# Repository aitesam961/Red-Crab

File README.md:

# Red-Crab: An Open Source, Modular PID controller.
RED-CRAB is an Open Source PID Controller designed for easy and flexible prototyping with PID controllers.
Offering vast selection of control parameters, this Project could be implemented in applications from hobbyist projects to home devices to industrial equipment where closed loop systems are required.

The idea of this project is to use a modular approach where different ad-ons could be used with the Basic PID controller board for controlling applications. Add-on Boards will be designed next added to the repository.
(OSHW Community can contribute in designing add-ons).

## Preview

## Table of contents
* [Red-Crab Overview](https://github.com/aitesam961/Red-Crab/blob/main/README.md#red-crab-overview)
* [How to Use:](https://github.com/aitesam961/Red-Crab/blob/main/README.md#how-to-use)
* [Electrical Specifications](https://github.com/aitesam961/Red-Crab/blob/main/README.md#electrical-specifications)
* [Build Your Own?](https://github.com/aitesam961/Red-Crab/blob/main/README.md#build-your-own)
* [Future Plans](https://github.com/aitesam961/Red-Crab/blob/main/README.md#future-plans)
* [Ordering Info](https://github.com/aitesam961/Red-Crab/blob/main/README.md#ordering-info)
* [Frequently Asked Questions(FAQs)](https://github.com/aitesam961/Red-Crab/blob/main/README.md#frequently-asked-questionsfaqs)
* [General Component Info](https://github.com/aitesam961/Red-Crab/blob/main/README.md#general-component-info)
* [Acknowledgements](https://github.com/aitesam961/Red-Crab/blob/main/README.md#acknowledgements)
* [License](https://github.com/aitesam961/Red-Crab/blob/main/README.md#license)

# Red-Crab Overview
### Features:
* Selectable P,PI,PID configurations.
* Adjustable GAINs using 50kOHM Potentiometers.
* DIP Switches for Controller Configuration
* Wide DC Voltage Input Range 
* 4-Layer Board with special Care to EMC/EMI for use in commercial applications.
* Open Source under GPL 3.0. (See License)
* Integrated Output Current Aplification for Larger Loads
* Ability to power External Peripherals

## How to Use:
## Electrical Specifications:

## Build Your Own?
## Future Plans
In future, this project seeks improvements and Development in following areas:
* Digital to Analog Converter Module (Ad-On Board)
* Temeprature Sensing & Amplification (Ad-On Board)
* Frequency to Voltage Converter (Ad-On Board)
* Integration with ARDUINO for Data Logging (Ad-On Board)
* Servo Actuation Control (Ad-On Board)
* Disturbance Integration Using Arduino (Ad-On Board)
## Ordering Info
You Can manufacture the PCBs from PCBWay.
[Check Out PCBWay](https://www.pcbway.com/setinvite.aspx?inviteid=440401)

Note: I am not affiliated with PCBWay. However, I just like their service and build quality.

## Frequently Asked Questions(FAQs)
## General Component Info

## Roadmap

* [x] Concept Proof
* [x] Research & Information
* [x] Finalizing The Idea
* [x] Schematics
* [x] PCB Design
* [ ] Validation & Testing
* [x] Documentation
* [ ] Future Improvements

### Contributions

Contributions are what make the open source community such an amazing place to learn, inspire, and create. Any contributions you make are **greatly appreciated**.

If you have a suggestion that would make this better, please fork the repo and create a pull request. You can also simply open an issue with the tag "enhancement".
Don't forget to give the project a star! Thanks again!

1. Fork the Project
2. Create your Feature Branch (`git checkout -b feature/AmazingFeature`)
3. Commit your Changes (`git commit -m 'Add some AmazingFeature'`)
4. Push to the Branch (`git push origin feature/AmazingFeature`)
5. Open a Pull Request

## Acknowledgements
This project is created to serve the Open Hardware Community in terms of Analog Controller Design using discrete components. Unfortunately, there isn't much of open source projects in terms of Flexible and Modular PID controller Design area.
Thye crater hopes it helps someone

## File Tree
```
.
├── Documents
│   ├── ibom.html
│   └── PID_Controller_Design.pdf
├── Images
│   ├── BOT1.png
│   ├── BOT1_RT.png
│   ├── PCB_1.png
│   ├── SID1_RT.png
│   ├── TOP1.png
│   ├── TOP1_RT.png
│   ├── TOP2_RT.png
│   ├── TOP3_RT.png
│   └── TOP4_RT.png
├── LICENSE.txt
├── Manufacturing Files
│   ├── bom.csv
│   ├── designators.csv
│   ├── gerber.zip
│   ├── netlist.ipc
│   └── positions.csv
├── MCAD Files
│   ├── Red-Crab.step
│   └── Red-Crab.wrl
├── README.md
├── Readme.txt.txt
├── References
│   ├── BananaSchplit-master
│   │   └── BananaSchplit-master
│   │       ├── assembly
│   │       │   ├── BananaSchplit-BOM.csv
│   │       │   └── BananaSchplit-Footprint-Positions.csv
│   │       ├── BananaSchplit-cache.lib
│   │       ├── BananaSchplit.kicad_pcb
│   │       ├── BananaSchplit.kicad_pcb-bak
│   │       ├── BananaSchplit.net
│   │       ├── BananaSchplit.pro
│   │       ├── BananaSchplit-rescue.dcm
│   │       ├── BananaSchplit-rescue.lib
│   │       ├── BananaSchplit.sch
│   │       ├── BananaSchplit.sch-bak
│   │       ├── BananaSchplit.xml
│   │       ├── fp-info-cache
│   │       ├── fp-lib-table
│   │       ├── gerber
│   │       │   ├── BananaSchplit-B_Cu.gbr
│   │       │   ├── BananaSchplit-B_Mask.gbr
│   │       │   ├── BananaSchplit-B_Paste.gbr
│   │       │   ├── BananaSchplit-B_SilkS.gbr
│   │       │   ├── BananaSchplit.drl
│   │       │   ├── BananaSchplit-Edge_Cuts.gbr
│   │       │   ├── BananaSchplit-F_Cu.gbr
│   │       │   ├── BananaSchplit-F_Mask.gbr
│   │       │   ├── BananaSchplit-F_Paste.gbr
│   │       │   ├── BananaSchplit-F_SilkS.gbr
│   │       │   └── BananaSchplit-Gerber.zip
│   │       ├── lib
│   │       │   ├── BananSchplitSilk.pretty
│   │       │   │   ├── BananaSchplitDrawn.png
│   │       │   │   ├── BananaSchplit.png
│   │       │   │   ├── BananaSchplitSilkLogoDrawn.kicad_mod
│   │       │   │   └── BananaSchplitSilkLogo.kicad_mod
│   │       │   ├── TPS65131RGET.lib
│   │       │   ├── TPS65131RGET.mod
│   │       │   └── TPS65131RGET.stp
│   │       ├── LICENSE
│   │       ├── README.md
│   │       └── sym-lib-table
│   ├── Screenshot 2022-07-08 204516.png
│   └── The_Design_of_the_PID_Controller.pdf
└── Source Files
    └── Red_Crab_KiCAD_Source
        ├── fp-info-cache
        ├── Passives.kicad_sch
        ├── PID_Core.kicad_sch
        ├── place_footprints.log
        ├── Power.kicad_sch
        ├── Red-Crab.kicad_pcb
        ├── Red-Crab.kicad_prl
        ├── Red-Crab.kicad_pro
        ├── Red-Crab.kicad_sch
        └── shapes3D
            ├── C_0603_1608Metric.wrl
            ├── C_0805_2012Metric.wrl
            ├── C_1206_3216Metric.wrl
            ├── CP_Elec_6.3x5.3.wrl
            ├── CP_Elec_6.3x7.7.wrl
            ├── DC-jack.wrl
            ├── D_SOD-123.wrl
            ├── Fuse_1210_3225Metric.wrl
            ├── HSOP-8-1EP_3.9x4.9mm_P1.27mm_EP2.41x3.1mm.wrl
            ├── HTSOP-8-1EP_3.9x4.9mm_Pitch1.27mm.wrl
            ├── JST_EH_S6B-EH_1x06_P2.50mm_Horizontal.wrl
            ├── L_Bourns_SRR1260.wrl
            ├── LED_0805_2012Metric.wrl
            ├── POT_SMD.wrl
            ├── QFN-24-1EP_4x4mm_P0.5mm_EP2.6x2.6mm.wrl
            ├── R_0402_1005Metric.wrl
            ├── R_0603_1608Metric.wrl
            ├── SOIC-14_3.9x8.7mm_P1.27mm.wrl
            ├── SOT-23.wrl
            └── SW_DIP_SPSTx08_Slide_6.7x21.88mm_W8.61mm_P2.54mm_LowProfile.wrl

14 directories, 87 files
```
## License
This Project is published under General Public License V3.0 See `LICENSE.txt` for more information.
> https://www.gnu.org/licenses/quick-guide-gplv3.html

<p align="right">(<a href="#top">back to top</a>)</p>

* [Jump To Start](https://github.com/maitesam/OpenADSP/blob/main/README.md#Description)

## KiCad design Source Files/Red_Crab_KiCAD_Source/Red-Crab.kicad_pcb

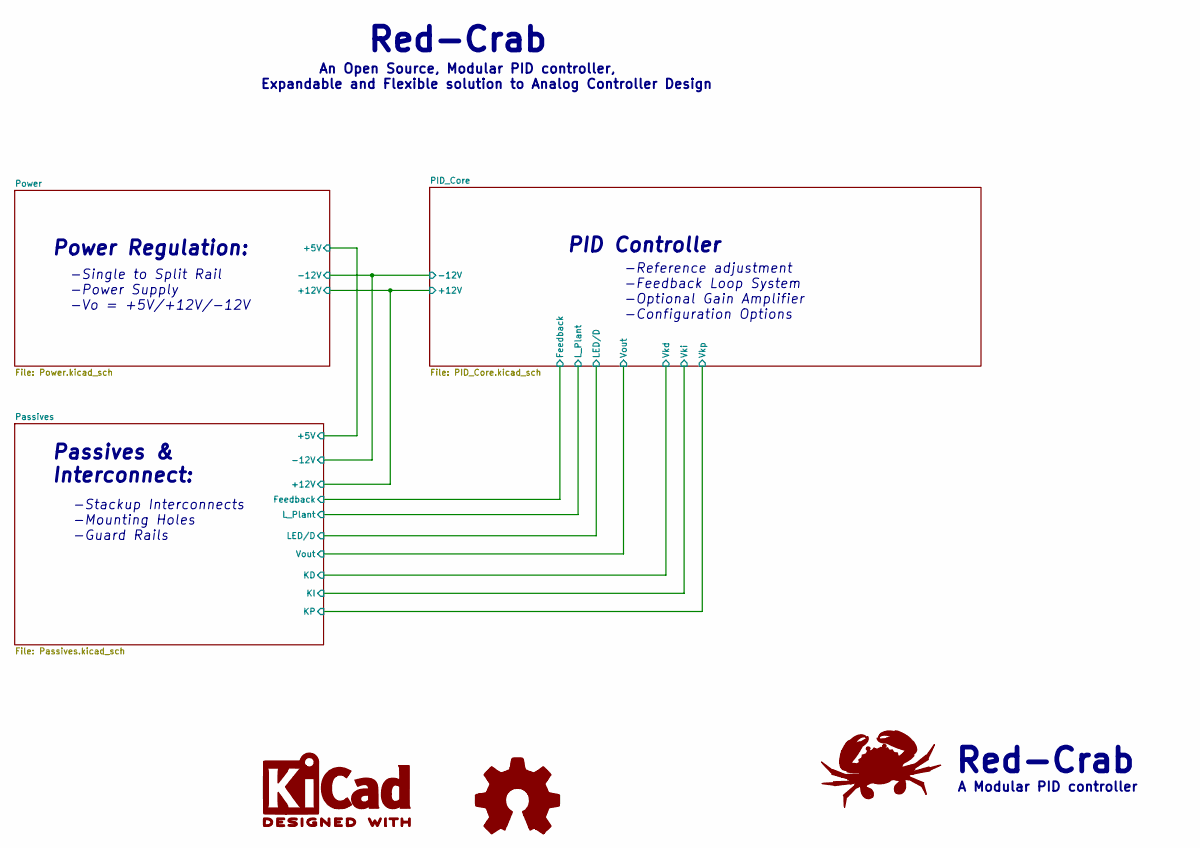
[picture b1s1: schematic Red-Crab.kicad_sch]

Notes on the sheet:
Passives & Interconnect:
An Open Source, Modular PID controller, Expandable and Flexible solution to Analog Controller Design
Red-Crab
PID Controller
Power Regulation:
-Single to Split Rail -Power Supply -Vo = +5V/+12V/-12V
A Modular PID controller
-Stackup Interconnects -Mounting Holes -Guard Rails
-Reference adjustment -Feedback Loop System -Optional Gain Amplifier -Configuration Options

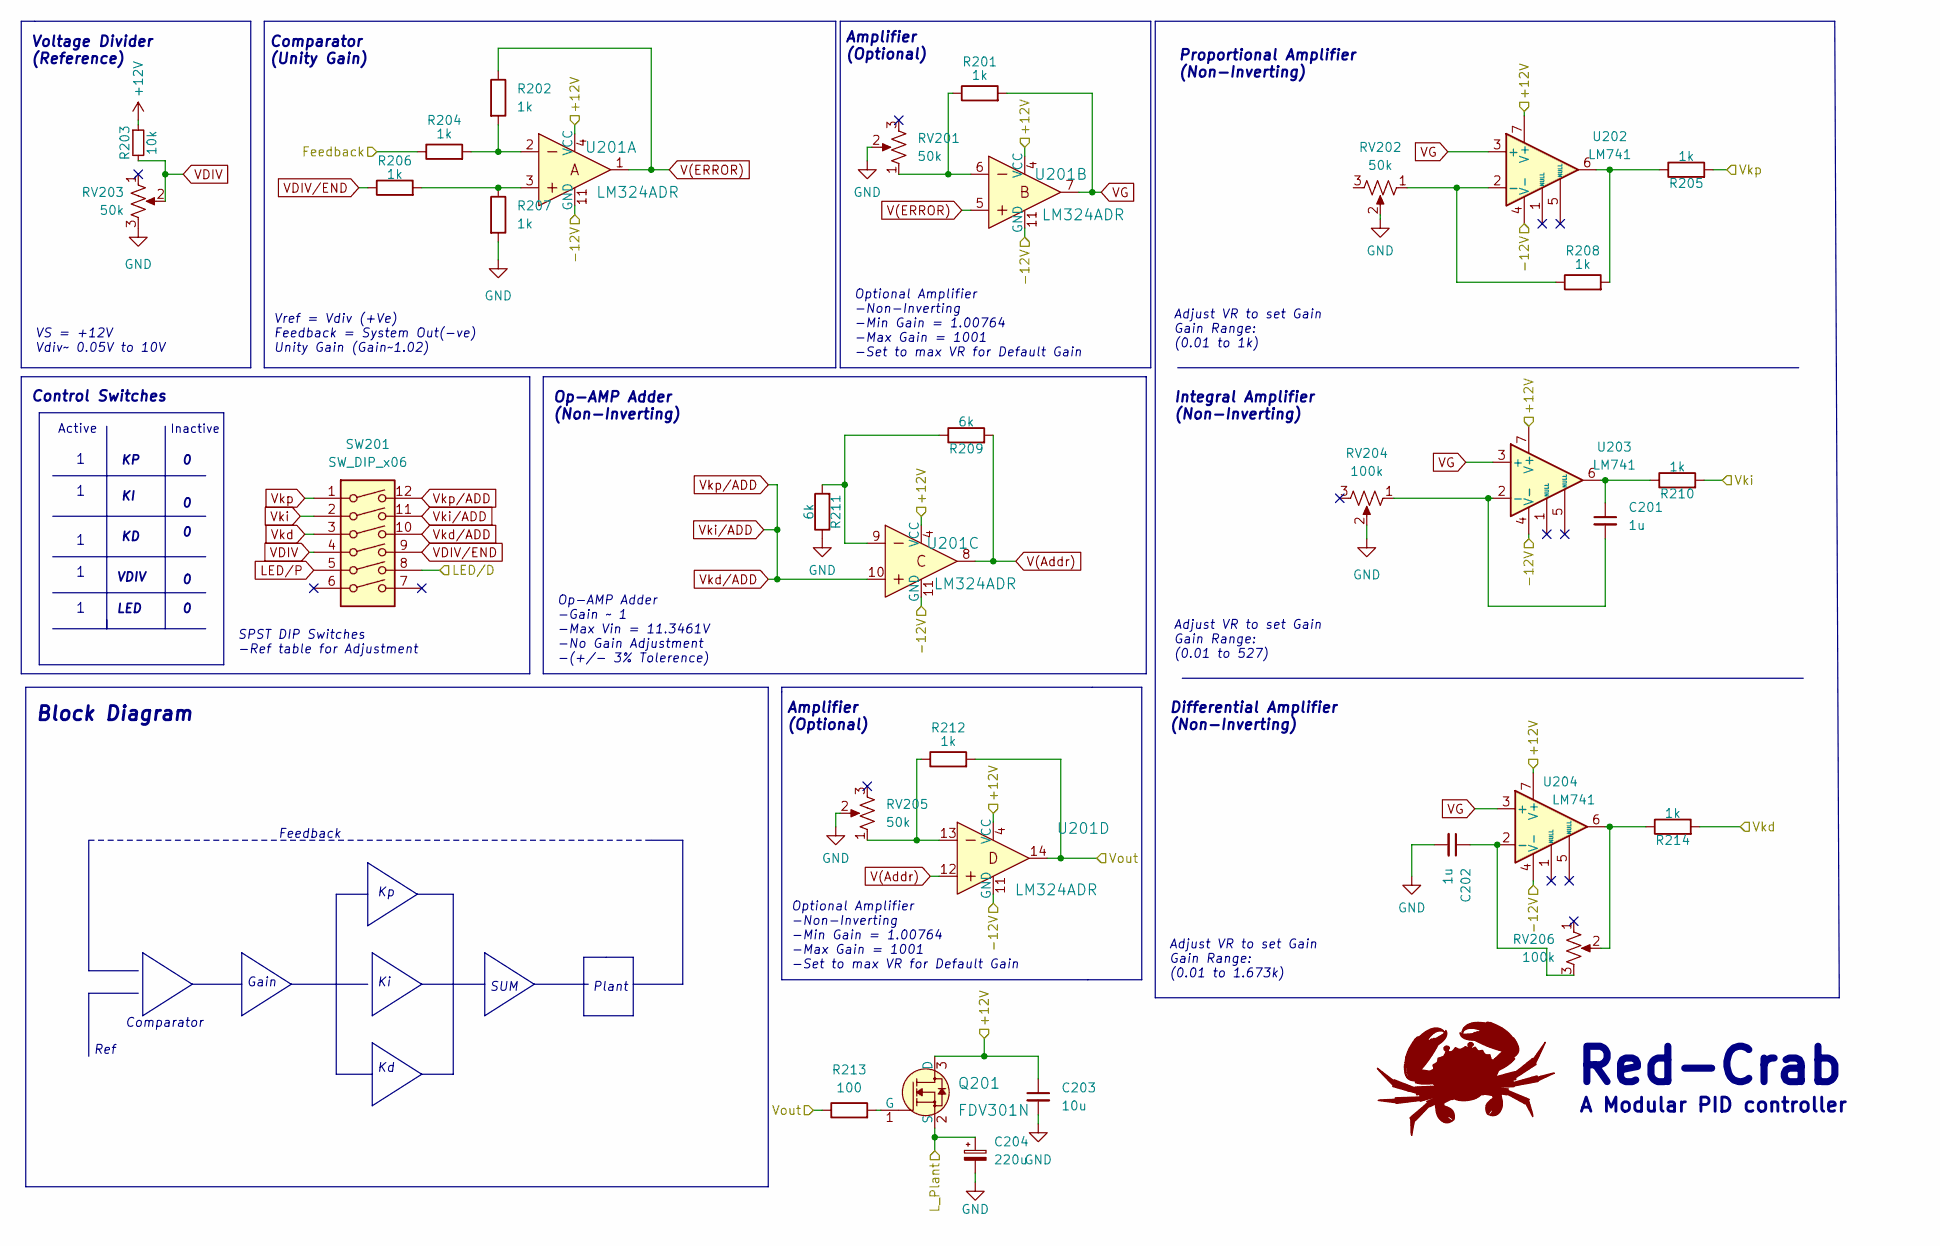
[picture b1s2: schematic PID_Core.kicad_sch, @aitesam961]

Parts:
C201, C202: 1u; C_1206_3216Metric; LCSC Part # C13585
C203: 10u; C_1206_3216Metric; LCSC Part # C13585
C204: 220u; CP_Elec_6.3x7.7; LCSC Part # C127327
Q201: FDV301N; SOT-23-3; MPN FDV301N; Digi-Key_PN FDV301NCT-ND
R201, R202, R204, R205, R206, R207, R208, R210, R212, R214: 1k; R_0402_1005Metric
R203: 10k; R_0603_1608Metric; LCSC Part # C22775
R209, R211: 6k; R_0402_1005Metric
R213: 100; R_0402_1005Metric
RV201, RV202, RV203, RV205: 50k; Potentiometer_Bourns_3214X_Vertical
RV204, RV206: 100k; Potentiometer_Bourns_3214X_Vertical
SW201: SW_DIP_x06; SW_DIP_SPSTx08_Slide_6.7x21.88mm_W8.61mm_P2.54mm_LowProfile
U201: LM324ADR; SOIC-14_W3.9mm; MPN LM324ADR; Digi-Key_PN 296-9540-1-ND
U202, U203, U204: LM741; SOP-8_3.76x4.96mm_P1.27mm

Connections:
+12V: C203.1, Q201.3 (D), R203.1, U201.4 (VCC), U202.7 (V+), U203.7 (V+), U204.7 (V+); also elsewhere on the board
-12V: U201.11 (GND), U202.4 (V-), U203.4 (V-), U204.4 (V-); also elsewhere on the board
/PID_Core/Feedback: R204.1; also elsewhere on the board
/PID_Core/LED/D: SW201.8; also elsewhere on the board
/PID_Core/L_Plant: C204.1, Q201.2 (S); also elsewhere on the board
/PID_Core/Vout: R212.2, R213.1, U201.14; also elsewhere on the board
GND: C202.2, C203.2, C204.2, R207.2, R211.1, RV201.2, RV202.2, RV203.3, RV204.2, RV205.2; also elsewhere on the board
LED/P: SW201.5
unnamed: C201.1, R210.1, U203.6
unnamed: C201.2, RV204.1, U203.2 (-)
unnamed: C202.1, RV206.3, U204.2 (-)
unnamed: Q201.1 (G), R213.2
unnamed: R201.1, RV201.1, U201.6
unnamed: R202.2, R204.2, U201.2
unnamed: R205.1, R208.2, U202.6
unnamed: R206.2, R207.1, U201.3
unnamed: R208.1, RV202.1, U202.2 (-)
unnamed: R209.1, R211.2, U201.9
unnamed: R212.1, RV205.1, U201.13
unnamed: R214.1, RV206.2, U204.6
V(Addr): R209.2, U201.8, U201.12
V(ERROR): R202.1, U201.1, U201.5
VDIV: R203.2, RV203.2, SW201.4
VDIV/END: R206.1, SW201.9
VG: R201.2, U201.7, U202.3 (+), U203.3 (+), U204.3 (+)
Vkd: R214.2, SW201.3; also elsewhere on the board
Vkd/ADD: SW201.10, SW201.11, SW201.12, U201.10
Vki: R210.2, SW201.2; also elsewhere on the board
Vkp: R205.2, SW201.1; also elsewhere on the board

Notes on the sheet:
Comparator (Unity Gain)
VDIV
Amplifier (Optional)
SUM
VS = +12V Vdiv~ 0.05V to 10V
Proportional Amplifier (Non-Inverting)
Optional Amplifier -Non-Inverting -Min Gain = 1.00764 -Max Gain = 1001 -Set to max VR for Default Gain
Op-AMP Adder (Non-Inverting)
Inactive
Block Diagram
Red-Crab
0 0
1 1
Ref
Integral Amplifier (Non-Inverting)
Op-AMP Adder -Gain ~ 1 -Max Vin = 11.3461V -No Gain Adjustment -(+/- 3% Tolerence)
Plant
Feedback
Adjust VR to set Gain Gain Range: (0.01 to 1.673k)
Voltage Divider (Reference)
Adjust VR to set Gain Gain Range: (0.01 to 527)
Control Switches
Vref = Vdiv (+Ve) Feedback = System Out(-ve) Unity Gain (Gain~1.02)
Gain
SPST DIP Switches -Ref table for Adjustment
LED
Active
Differential Amplifier (Non-Inverting)
A Modular PID controller
Adjust VR to set Gain Gain Range: (0.01 to 1k)
Comparator

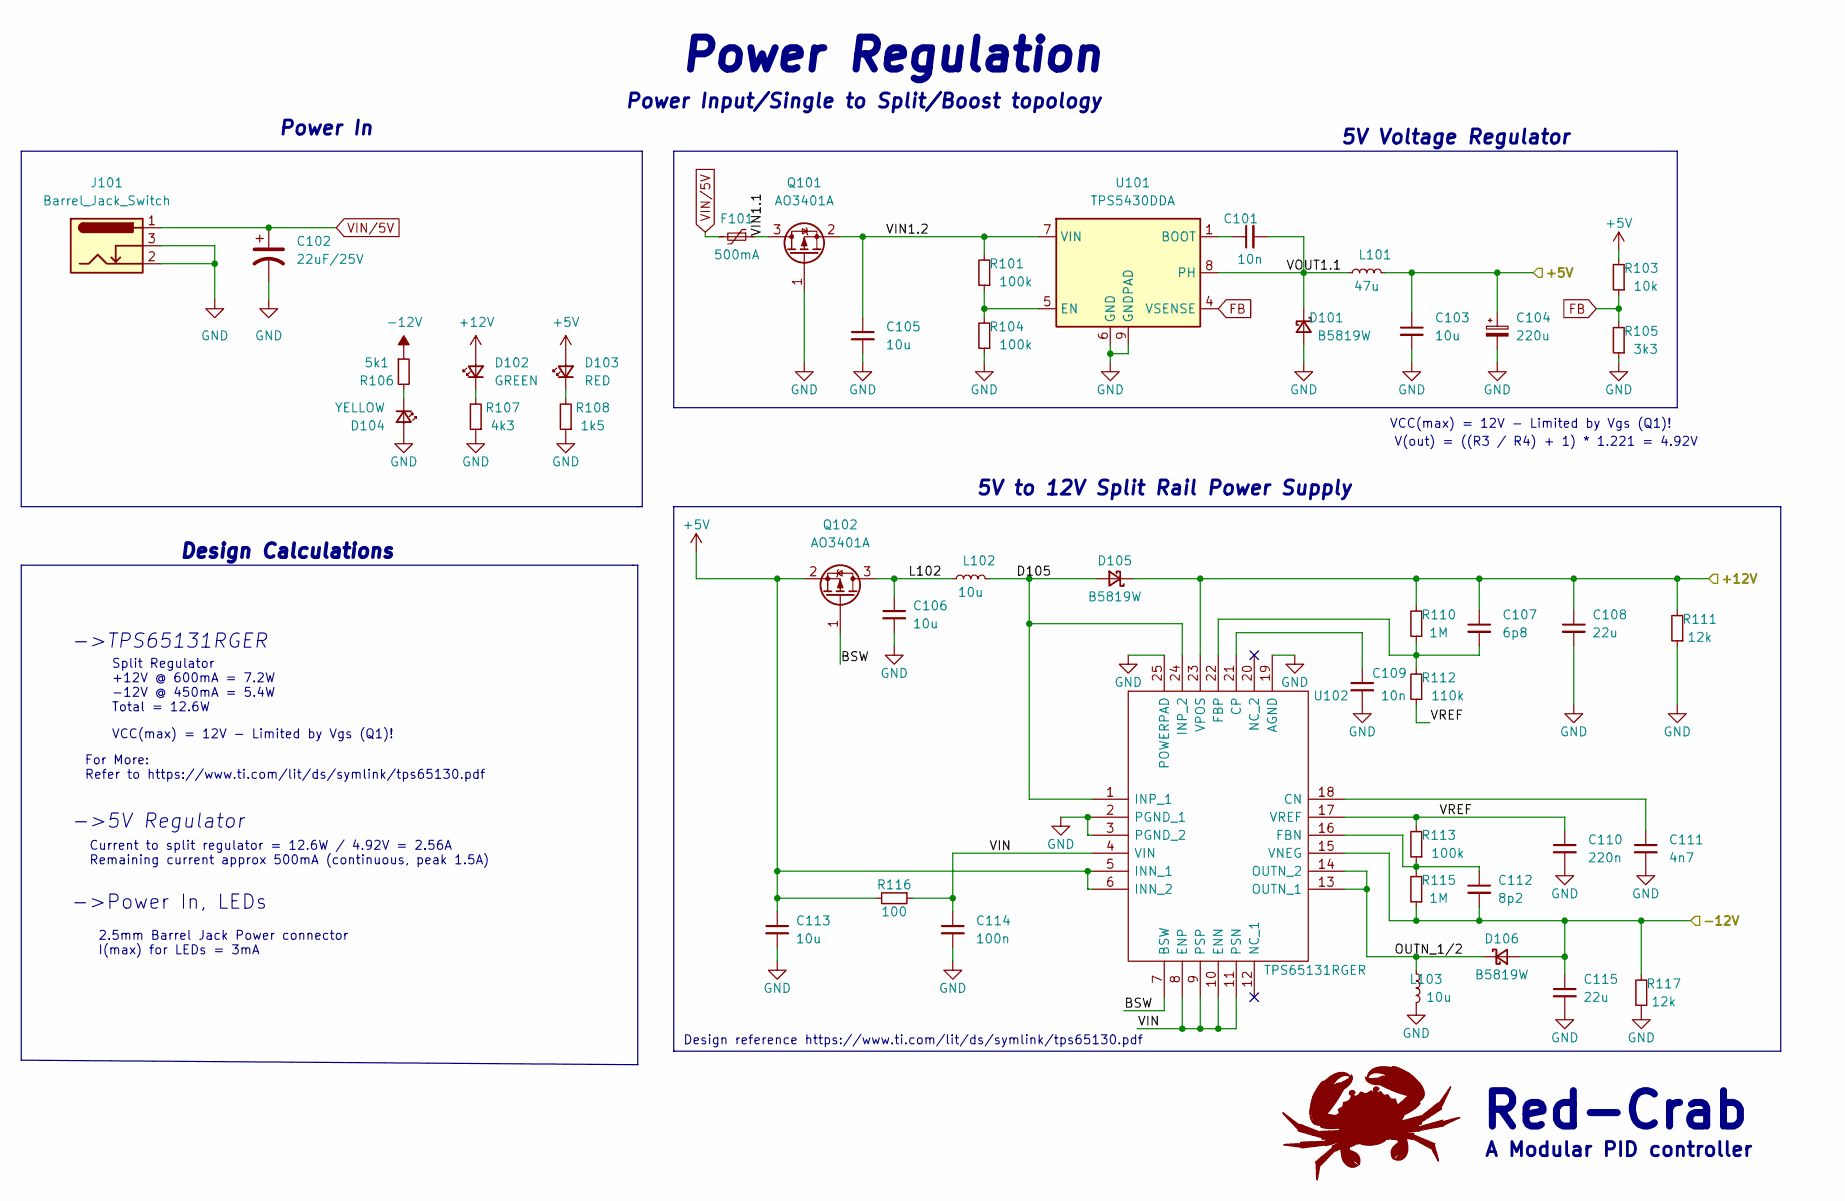
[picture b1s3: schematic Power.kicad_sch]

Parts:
C101, C109: 10n; C_0603_1608Metric; LCSC Part # C57112
C102: 22uF/25V; CP_Elec_6.3x5.3
C103, C105, C106, C113: 10u; C_1206_3216Metric; LCSC Part # C13585
C104: 220u; CP_Elec_6.3x7.7; LCSC Part # C127327
C107: 6p8; C_0603_1608Metric; LCSC Part # C1679
C108, C115: 22u; C_0805_2012Metric; LCSC Part # C45783
C110: 220n; C_0603_1608Metric; LCSC Part # C21120
C111: 4n7; C_0603_1608Metric; LCSC Part # C53987
C112: 8p2; C_0603_1608Metric; LCSC Part # C1685
C114: 100n; C_0603_1608Metric; LCSC Part # C14663
D101, D105, D106: B5819W; D_SOD-123; LCSC Part # C8598
D102: GREEN; LED_0805_2012Metric; LCSC Part # C2297
D103: RED; LED_0805_2012Metric; LCSC Part # C84256
D104: YELLOW; LED_0805_2012Metric; LCSC Part # C2296
F101: 500mA; Fuse_1812_4532Metric; LCSC Part # C151168
J101: Barrel_Jack_Switch; BarrelJack_GCT_DCJ200-10-A_Horizontal
L101: 47u; L_Sunlord_MWSA0518_5.4x5.2mm; LCSC Part # C169398
L102, L103: 10u; L_Sunlord_MWSA0518_5.4x5.2mm; LCSC Part # C139506
Q101, Q102: AO3401A; SOT-23; LCSC Part # C15127
R101, R104, R113: 100k; R_0603_1608Metric; LCSC Part # C25803
R103: 10k; R_0603_1608Metric; LCSC Part # C25804
R105: 3k3; R_0603_1608Metric; LCSC Part # C22978
R106: 5k1; R_0603_1608Metric; LCSC Part # C23186
R107: 4k3; R_0603_1608Metric; LCSC Part # C23159
R108: 1k5; R_0603_1608Metric; LCSC Part # C22843
R110, R115: 1M; R_0603_1608Metric; LCSC Part # C22935
R111, R117: 12k; R_0603_1608Metric; LCSC Part # C22790
R112: 110k; R_0603_1608Metric; LCSC Part # C25805
R116: 100; R_0603_1608Metric; LCSC Part # C22775
U101: TPS5430DDA; TI_SO-PowerPAD-8_ThermalVias; LCSC Part # C9864
U102: TPS65131RGER; QFN-24-1EP_4x4mm_P0.5mm_EP2.6x2.6mm; Mouser2 Part Number 595-TPS65131RGET

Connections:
+5V: C103.1, C104.1, C113.1, D103.2 (A), L101.2, Q102.2 (S), R103.2, R116.2, U102.5 (INN_1), U102.6 (INN_2); also elsewhere on the board
+12V: C107.1, C108.1, D102.2 (A), D105.1 (K), R110.2, R111.2, U102.23 (VPOS); also elsewhere on the board
-12V: C112.2, C115.1, D106.2 (A), R106.1, R115.1, R117.2, U102.15 (VNEG); also elsewhere on the board
/Power/BSW: Q102.1 (G), U102.7 (BSW)
/Power/D105: D105.2 (A), L102.2, U102.1 (INP_1), U102.24 (INP_2)
/Power/L102: C106.1, L102.1, Q102.3 (D)
/Power/OUTN_1/2: D106.1 (K), L103.1, U102.13 (OUTN_1), U102.14 (OUTN_2)
/Power/VIN: C114.1, R116.1, U102.4 (VIN), U102.8 (ENP), U102.9 (PSP), U102.10 (ENN), U102.11 (PSN)
/Power/VIN1.1: F101.1, Q101.3 (D)
/Power/VIN1.2: C105.1, Q101.2 (S), R101.2, U101.7 (VIN)
/Power/VOUT1.1: C101.2, D101.1 (K), L101.1, U101.8 (PH)
/Power/VREF: C110.1, R112.1, R113.2, U102.17 (VREF)
FB: R103.1, R105.2, U101.4 (VSENSE)
GND: C102.2, C103.2, C104.2, C105.2, C106.2, C108.2, C109.2, C110.2, C111.2, C113.2, C114.2, C115.2, D101.2 (A), D104.2 (A), J101.2, J101.3, L103.2, Q101.1 (G), R104.1, R105.1, R107.1, R108.1, R111.1, R117.1, U101.6 (GND), U101.9 (GNDPAD), U102.2 (PGND_1), U102.3 (PGND_2), U102.19 (AGND), U102.25 (POWERPAD); also elsewhere on the board
unnamed: C101.1, U101.1 (BOOT)
unnamed: C107.2, R110.1, R112.2, U102.22 (FBP)
unnamed: C109.1, U102.21 (CP)
unnamed: C111.1, U102.18 (CN)
unnamed: C112.1, R113.1, R115.2, U102.16 (FBN)
unnamed: D102.1 (K), R107.2
unnamed: D103.1 (K), R108.2
unnamed: D104.1 (K), R106.2
unnamed: R101.1, R104.2, U101.5 (EN)
VIN/5V: C102.1, F101.2, J101.1

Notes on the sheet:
Design reference https://www.ti.com/lit/ds/symlink/tps65130.pdf
Split Regulator +12V @ 600mA = 7.2W -12V @ 450mA = 5.4W Total = 12.6W
Design Calculations
->5V Regulator
A Modular PID controller
Power Input/Single to Split/Boost topology
V(out) = ((R3 / R4) + 1) * 1.221 = 4.92V
5V Voltage Regulator
5V to 12V Split Rail Power Supply
->TPS65131RGER
VCC(max) = 12V - Limited by Vgs (Q1)!
Red-Crab
Current to split regulator = 12.6W / 4.92V = 2.56A Remaining current approx 500mA (continuous, peak 1.5A)
->Power In, LEDs
Power In
For More: Refer to https://www.ti.com/lit/ds/symlink/tps65130.pdf
Power Regulation
2.5mm Barrel Jack Power connector I(max) for LEDs = 3mA

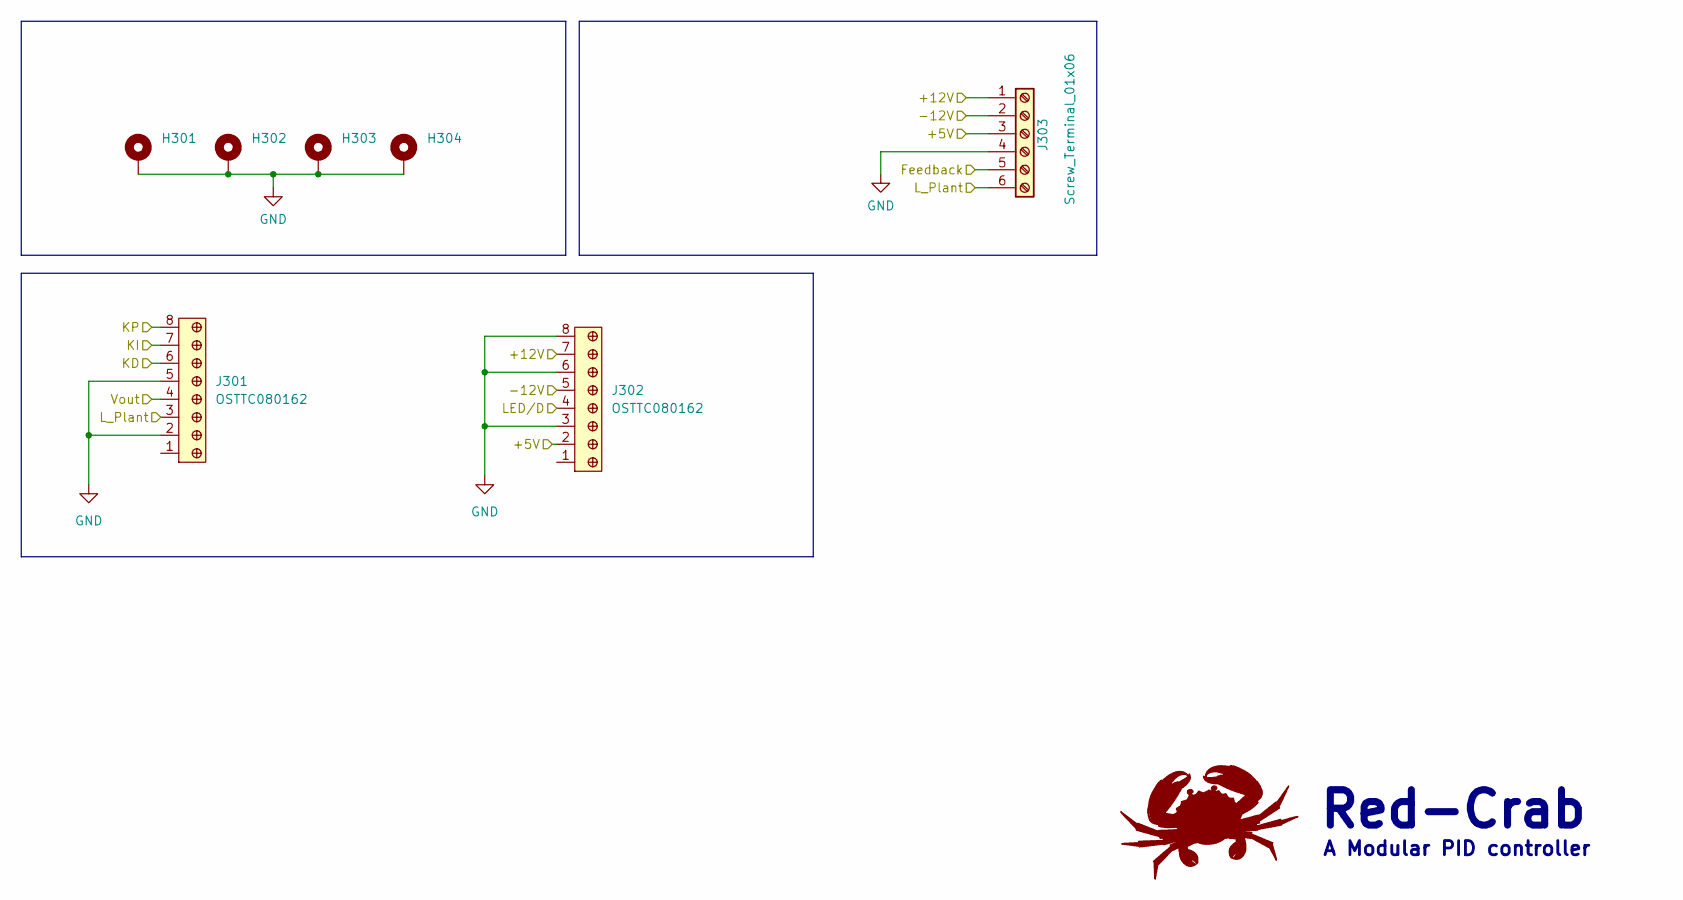
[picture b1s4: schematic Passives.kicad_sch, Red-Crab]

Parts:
H301, H302, H303, H304: MountingHole_Pad; MountingHole_2.2mm_M2_Pad_Via
J301, J302: OSTTC080162; PinHeader_1x08_P1.27mm_Vertical_SMD_Pin1Left; MPN OSTTC080162; Digi-Key_PN ED2606-ND
J303: Screw_Terminal_01x06; Stocko_MKS_1656-6-0-606_1x6_P2.50mm_Vertical

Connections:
+5V: J302.2, J303.3; also elsewhere on the board
+12V: J302.7, J303.1; also elsewhere on the board
-12V: J302.5, J303.2; also elsewhere on the board
/PID_Core/Feedback: J303.5; also elsewhere on the board
/PID_Core/LED/D: J302.4; also elsewhere on the board
/PID_Core/L_Plant: J301.3, J303.6; also elsewhere on the board
/PID_Core/Vout: J301.4; also elsewhere on the board
GND: H301.1, H302.1, H303.1, H304.1, J301.2, J301.5, J302.3, J302.6, J302.8, J303.4; also elsewhere on the board
Vkd: J301.6; also elsewhere on the board
Vki: J301.7; also elsewhere on the board
Vkp: J301.8; also elsewhere on the board

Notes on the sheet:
Red-Crab
A Modular PID controller

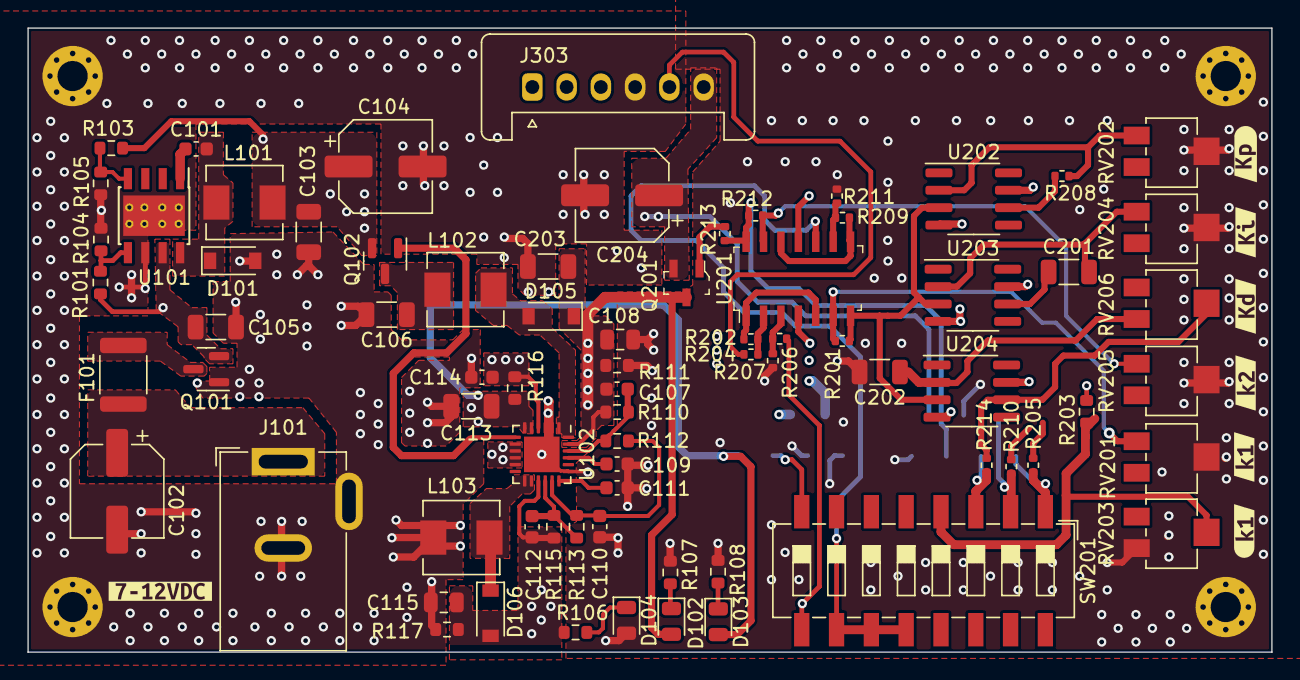
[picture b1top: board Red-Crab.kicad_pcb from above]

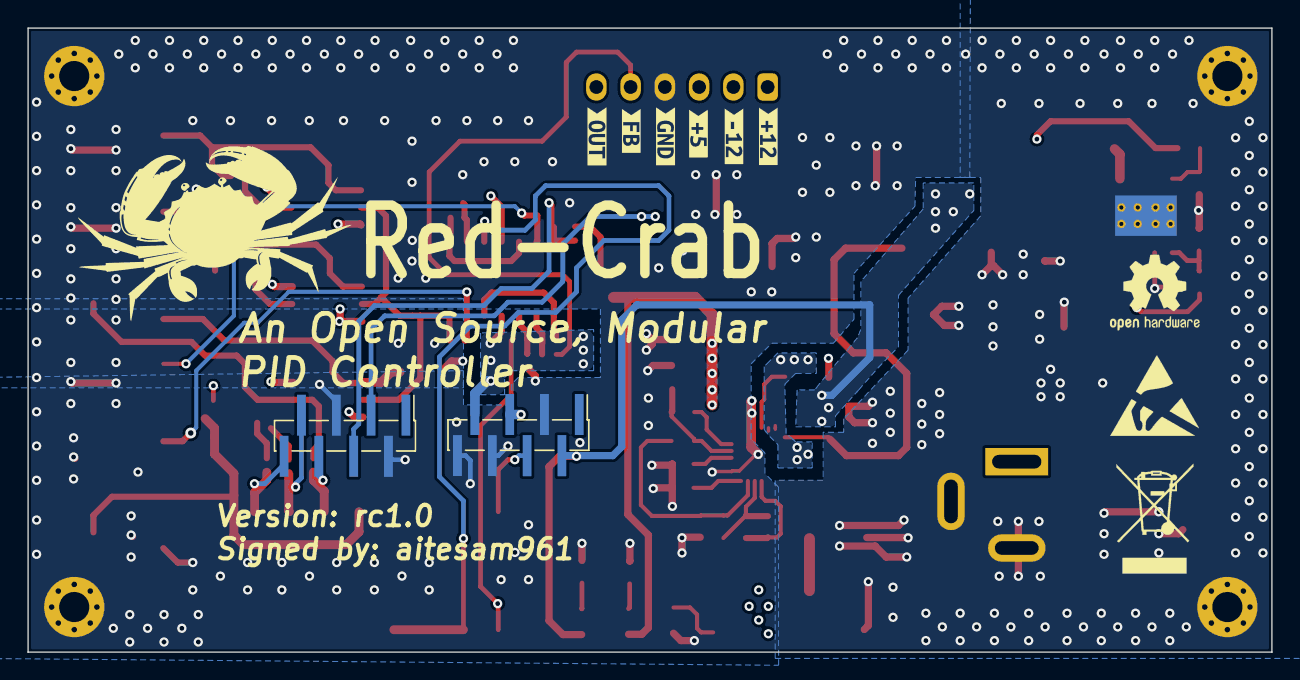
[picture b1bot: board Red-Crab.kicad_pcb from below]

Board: 4 copper layers, 90.8 x 45.5 mm, 94 parts (8 on the bottom side), 49 nets.

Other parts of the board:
kibuzzard-62D28A8A: G***; kibuzzard-62D28A8A
kibuzzard-62D28A66: G***; kibuzzard-62D28A66
kibuzzard-62D28AAB: G***; kibuzzard-62D28AAB
kibuzzard-62D28AD0: G***; kibuzzard-62D28AD0
kibuzzard-62D28B16: G***; kibuzzard-62D28B16
kibuzzard-62D28BAA: G***; kibuzzard-62D28BAA
kibuzzard-62D28C0C: G***; kibuzzard-62D28C0C
kibuzzard-62D562E5: G***; kibuzzard-62D562E5
kibuzzard-62D5635A: G***; kibuzzard-62D5635A
kibuzzard-62D5638B: G***; kibuzzard-62D5638B
kibuzzard-62D56315: G***; kibuzzard-62D56315
kibuzzard-62D56342: G***; kibuzzard-62D56342
kibuzzard-62D56368: G***; kibuzzard-62D56368

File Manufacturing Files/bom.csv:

Designator,Footprint,Quantity,Value,LCSC Part #
J303,Stocko_MKS_1656-6-0-606_1x6_P2.50mm_Vertical,1,Screw_Terminal_01x06,
RV204,Potentiometer_Bourns_3214X_Vertical,1,100k,
RV203,Potentiometer_Bourns_3214X_Vertical,1,50k,
U203,SOP-8_3.76x4.96mm_P1.27mm,1,LM741,
C105,C_1206_3216Metric,1,10u,C13585
R117,R_0603_1608Metric,1,12k,C22790
U204,SOP-8_3.76x4.96mm_P1.27mm,1,LM741,
Q101,SOT-23,1,AO3401A,C15127
C103,C_1206_3216Metric,1,10u,C13585
C113,C_1206_3216Metric,1,10u,C13585
R205,R_0402_1005Metric,1,1k,
H302,MountingHole_2.2mm_M2_Pad_Via,1,MountingHole_Pad,
RV206,Potentiometer_Bourns_3214X_Vertical,1,100k,
C101,C_0603_1608Metric,1,10n,C57112
R213,R_0402_1005Metric,1,100,
R106,R_0603_1608Metric,1,5k1,C23186
R202,R_0402_1005Metric,1,1k,
D104,LED_0805_2012Metric,1,YELLOW,C2296
R111,R_0603_1608Metric,1,12k,C22790
C109,C_0603_1608Metric,1,10n,C57112
R107,R_0603_1608Metric,1,4k3,C23159
D105,D_SOD-123,1,B5819W,C8598
R212,R_0402_1005Metric,1,1k,
U202,SOP-8_3.76x4.96mm_P1.27mm,1,LM741,
D101,D_SOD-123,1,B5819W,C8598
C102,CP_Elec_6.3x5.3,1,22uF/25V,
RV202,Potentiometer_Bourns_3214X_Vertical,1,50k,
R203,R_0603_1608Metric,1,10k,C22775
H301,MountingHole_2.2mm_M2_Pad_Via,1,MountingHole_Pad,
C204,CP_Elec_6.3x7.7,1,220u,C127327
J101,BarrelJack_GCT_DCJ200-10-A_Horizontal,1,Barrel_Jack_Switch,
R104,R_0603_1608Metric,1,100k,C25803
C104,CP_Elec_6.3x7.7,1,220u,C127327
R207,R_0402_1005Metric,1,1k,
H304,MountingHole_2.2mm_M2_Pad_Via,1,MountingHole_Pad,
Q201,SOT-23-3,1,FDV301N,FDV301N
Q102,SOT-23,1,AO3401A,C15127
R204,R_0402_1005Metric,1,1k,
C201,C_1206_3216Metric,1,1u,C13585
C202,C_1206_3216Metric,1,1u,C13585
R105,R_0603_1608Metric,1,3k3,C22978
R201,R_0402_1005Metric,1,1k,
L101,L_Sunlord_MWSA0518_5.4x5.2mm,1,47u,C169398
R116,R_0603_1608Metric,1,100,C22775
U101,TI_SO-PowerPAD-8_ThermalVias,1,TPS5430DDA,C9864
C106,C_1206_3216Metric,1,10u,C13585
R113,R_0603_1608Metric,1,100k,C25803
R210,R_0402_1005Metric,1,1k,
R110,R_0603_1608Metric,1,1M,C22935
R206,R_0402_1005Metric,1,1k,
R103,R_0603_1608Metric,1,10k,C25804
C110,C_0603_1608Metric,1,220n,C21120
L103,L_Sunlord_MWSA0518_5.4x5.2mm,1,10u,C139506
R115,R_0603_1608Metric,1,1M,C22935
D103,LED_0805_2012Metric,1,RED,C84256
R112,R_0603_1608Metric,1,110k,C25805
C107,C_0603_1608Metric,1,6p8,C1679
RV201,Potentiometer_Bourns_3214X_Vertical,1,50k,
SW201,SW_DIP_SPSTx08_Slide_6.7x21.88mm_W8.61mm_P2.54mm_LowProfile,1,SW_DIP_x06,
C203,C_1206_3216Metric,1,10u,C13585
L102,L_Sunlord_MWSA0518_5.4x5.2mm,1,10u,C139506
C115,C_0805_2012Metric,1,22u,C45783
C114,C_0603_1608Metric,1,100n,C14663
H303,MountingHole_2.2mm_M2_Pad_Via,1,MountingHole_Pad,
C112,C_0603_1608Metric,1,8p2,C1685
R101,R_0603_1608Metric,1,100k,C25803
R208,R_0402_1005Metric,1,1k,
F101,Fuse_1812_4532Metric,1,500mA,C151168
D102,LED_0805_2012Metric,1,GREEN,C2297
C111,C_0603_1608Metric,1,4n7,C53987
D106,D_SOD-123,1,B5819W,C8598
R214,R_0402_1005Metric,1,1k,
R209,R_0402_1005Metric,1,6k,
C108,C_0805_2012Metric,1,22u,C45783
R211,R_0402_1005Metric,1,6k,
U102,QFN-24-1EP_4x4mm_P0.5mm_EP2.6x2.6mm,1,TPS65131RGER,C87663
U201,SOIC-14_W3.9mm,1,LM324ADR,LM324ADR
R108,R_0603_1608Metric,1,1k5,C22843
RV205,Potentiometer_Bourns_3214X_Vertical,1,50k,
J302,PinHeader_1x08_P1.27mm_Vertical_SMD_Pin1Left,1,OSTTC080162,OSTTC080162
J301,PinHeader_1x08_P1.27mm_Vertical_SMD_Pin1Left,1,OSTTC080162,OSTTC080162

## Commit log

2023-12-01 Add image preview to `Readme.md`
